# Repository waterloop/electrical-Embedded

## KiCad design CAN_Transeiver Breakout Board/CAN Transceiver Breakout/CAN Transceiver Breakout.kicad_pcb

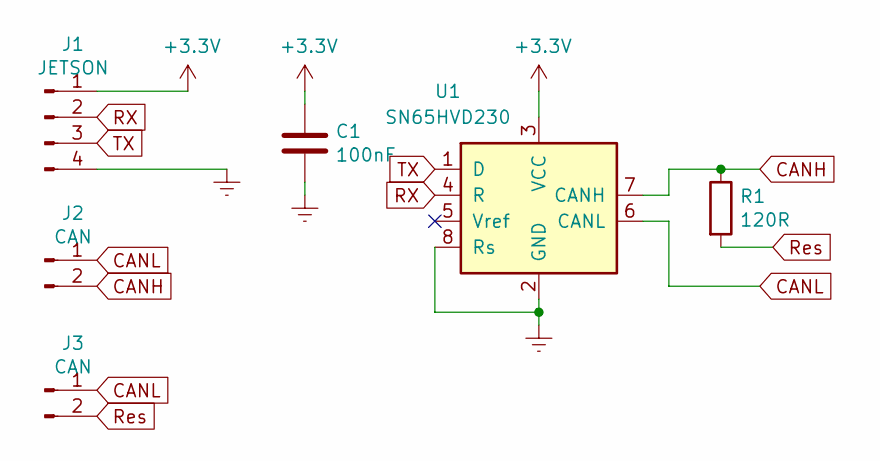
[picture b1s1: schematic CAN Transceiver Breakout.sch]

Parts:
C1: 100nF; C_0805_2012Metric
J1: JETSON; JST_EH_B4B-EH-A_1x04_P2.50mm_Vertical
J2, J3: CAN; JST_EH_B2B-EH-A_1x02_P2.50mm_Vertical
R1: 120R; R_0201_0603Metric
U1: SN65HVD230; SOIC-8_3.9x4.9mm_P1.27mm

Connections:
+3V3: C1.1, J1.1, U1.3 (VCC)
CANH: J2.2, R1.1, U1.7 (CANH)
CANL: J2.1, J3.1, U1.6 (CANL)
Earth: C1.2, J1.4, U1.2 (GND), U1.8 (Rs)
RX: J1.2, U1.4 (R)
Res: J3.2, R1.2
TX: J1.3, U1.1 (D)

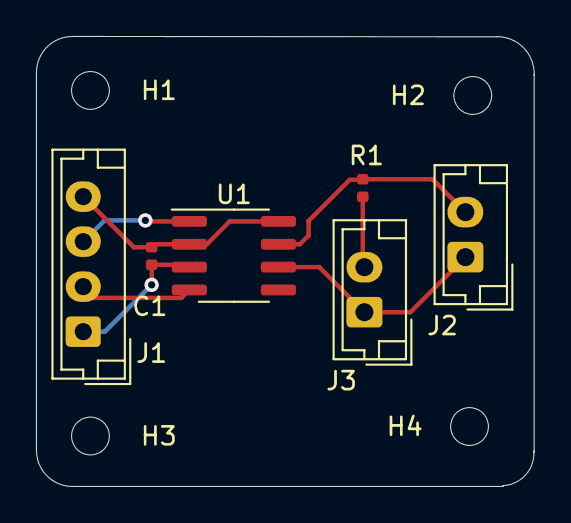
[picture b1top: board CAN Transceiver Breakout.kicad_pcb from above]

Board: 2 copper layers, 27.7 x 25.0 mm, 10 parts (0 on the bottom side), 7 nets.

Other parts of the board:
H1, H2, H3, H4: MountingHole_2.1mm

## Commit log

2020-09-04 the beginning
2020-09-05 delibird components set up
2020-09-05 replaced crystal oscillator
2020-09-05 updated with tja1051/3118
2020-09-05 10-pin header
2020-09-05 connected ics
2020-09-05 added headers
2020-09-05 added spi and i2c pins for testing
2020-09-06 finished layout, some clearance errors
2020-09-07 Final
2020-09-07 Adding Outjob for PCB Manufacturing
    - Added outjob for JLCPCB order
    - Added board outline to Mechanical 1 layer
2020-09-12 Elekid Altium Redo, schematic pending a few final edits & review
2020-09-12 updated PDF in prep for review
2020-09-12 a few fixes
2020-09-12 fixed 24v net placement
2020-09-13 Finished layout, pending review
2020-09-13 Put names on the board
2020-10-07 Update Outjob for Assembly
2020-10-14 added adt7311 to libraries
2020-10-17 Added folder for step files
2020-10-27 Create test
2020-10-27 Added Pressure Sensing Board
2020-10-30 phototransistors added to library
2020-10-31 delibird and psyduck step files updated
2020-10-31 PCB board size expanded for psyduck and belibird to accommodate bigger mounting holes
2020-11-01 Added submodule for general library and updated PCB
2020-11-03 Temperature Sensor Updated
2020-11-03 Enlarged mounting holes on temperature sensor, shifted stuff around to do so, and added its step file
2020-11-04 Mechanical Layer 1 Fix + Gerber File added
2020-11-04 configured outjob files for temperature sensor
2020-11-07 Added the Gerber Files to the Folder
2020-11-07 Added Gerner Files to Psyduck
2020-11-14 shifted ring encoder mounting hole left
2020-11-27 Elekid Rev 2 Completed
2020-11-28 step files uploaded
2020-11-28 breakoutboard step
2020-11-28 mounting holes for step files added
2020-12-04 Elekid project outputs
2020-12-04 Elekid Breakout Board Project Outputs
2020-12-04 proj output fix
2020-12-04 project update
2020-12-04 added logo, regenerated gerbs
2020-12-04 slight fix
2021-03-21 Updated temp sensor schematic with updated library
2021-03-21 made changes
2021-03-21 fixing this kid
2021-03-22 Updated Psyduck
    Added more headers to accommodate 3 pressure sensors at maximum, etc.
2021-03-24 Implemented most of the design changes to schematic
2021-03-25 did a thing to psyduck
2021-03-25 did stuff
2021-03-25 Created STEP file
2021-03-25 Finished layout
2021-03-27 Added firmware code
2021-03-28 Added line to convert voltage to current.
2021-03-28 Added temperature sensor firmware
2021-03-28 Updated firmware code errors
2021-04-01 Started Elekid_MCU schematic and created an outjob with PDF
    Should be known that only the first two pages on the outjob pdf are relevant as the PCB has not been laid out properly at all yet.
2021-04-02 Finished schematic and started layout of Elekid MCU
2021-04-02 Generated project output files for elekid MCU
2021-04-03 finished elekid power schematic, created pcb doc
2021-04-03 worked on placement
2021-04-05 worked on component placement
2021-04-05 moved components closer, added note on schematic
2021-04-06 worked on routing, tried a different layout
2021-04-07 moved things around
2021-04-07 made components closer, added gnd layer, attempted differential pair routing
2021-04-08 updated layout of Elekid MCU pcb
2021-04-10 replaced connectors, added gnd, changed file name
2021-04-10 moved traces a bit & repoured
2021-04-10 changed footprints for some components
2021-04-10 made power trace thicker
2021-04-10 pour gnd on top layer & removed gnd traces
2021-04-10 libraries added to pcb project
2021-04-10 add libraries
2021-04-10 net ties go brrr
2021-04-10 Finished PCB layout and exported all project documents
2021-04-10 Updating final project documents
2021-04-11 added connects, vias for routing, polygon pour over top and bot layers
2021-04-11 made power traces thicc
2021-04-11 added supplier part numbers for MOST (not all) components
2021-04-11 BOM created (needs review tho)
2021-04-11 make inductor traces thicker
2021-04-13 made power routing straighter, moved fuse, labelling, pours
2021-04-13 fixed pour connect type
2021-04-14 added vias, moved some silks
2021-04-14 moved silks
2021-04-14 changed C6 to 1206 footprint & BOM
2021-04-14 Finished code for Elekid MCU
2021-04-14 Removed double repo
2021-04-14 added connectors to BOM
2021-04-14 added gerber files
2021-04-15 Updated layout and ran ERC
2021-04-15 updated BOM
2021-04-25 Updated code
2021-06-12 initialize yamper project
2021-06-12 initializing yamper pt2
2021-06-12 add yamper ICs
2021-06-12 add phototransistor to yamper schematic
2021-06-13 added pdf
2021-06-13 fix yamper schematic
2021-06-13 Add files via upload
    PDF
2021-06-15 adjust yamper based on schematic roast
2021-06-16 add yamper preview
2021-06-16 added CAN resistors to Yamper schematic
2021-06-16 add component libraries
2021-06-16 change layout of yamper schematic
2021-06-17 add yamper test points
2021-06-17 updated schematic
2021-06-19 fix schematic and start layout
2021-06-19 (yamper): add updated schematic
2021-06-19 inital Staravia commit
2021-06-19 updated to new libraries
2021-06-19 brrr
2021-06-19 added pcb
2021-06-19 figured out dimensions for RPI
2021-06-19 (yamper): finish layout v1
2021-06-19 forcing push go brrrrr
2021-06-22 update based on roast
2021-06-22 PIL initial
2021-06-23 added BOM
2021-06-23 I give up
2021-06-24 Staravia Pcb
2021-06-24 add yamper image
2021-06-24 meme
2021-06-25 finish yamper!
2021-06-25 change mounting hole size to 3.4mm
2021-06-26 initialize yamper stm32 project
2021-06-26 add function to compute rpm
2021-06-28 done sort of
2021-06-28 Done
2021-06-28 done again
2021-06-29 MCU schematic
2021-06-30 MCU schematic (actual)
2021-06-30 yay :))
2021-07-01 added staravia keep-out layer, gerbers
2021-07-08 generated delibird and yamper step files
2021-07-17 add can driver code
2021-07-17 blink led with interrupt
2021-07-17 Yamper (#3)
    * add yamper image
    * finish yamper!
    * change mounting hole size to 3.4mm
    * initialize yamper stm32 project
    * add function to compute rpm
    * add can driver code
2021-08-10 made some changes
2021-08-13 LED test code
2021-09-16 Updating Elekid files with latest updated ones
    Working Elekid files being updated in the repo.
2021-10-15 added some stuff
2021-10-15 prelim psyduck and torchic code
2021-10-16 initial
2021-10-28 thingy to fix a thingy
2021-11-03 I did a thing
2021-12-05 adding st link adapter board project
2021-12-28 CAN transceiver
    Adding updated CAN transceiver board
2021-12-28 Remade CAN Transceiver in altium
2021-12-28 created basic layout
2021-12-29 finished can board
    added in silk layer, gerber and the pdf
2022-01-17 created CAN hub and edited Transceiver
